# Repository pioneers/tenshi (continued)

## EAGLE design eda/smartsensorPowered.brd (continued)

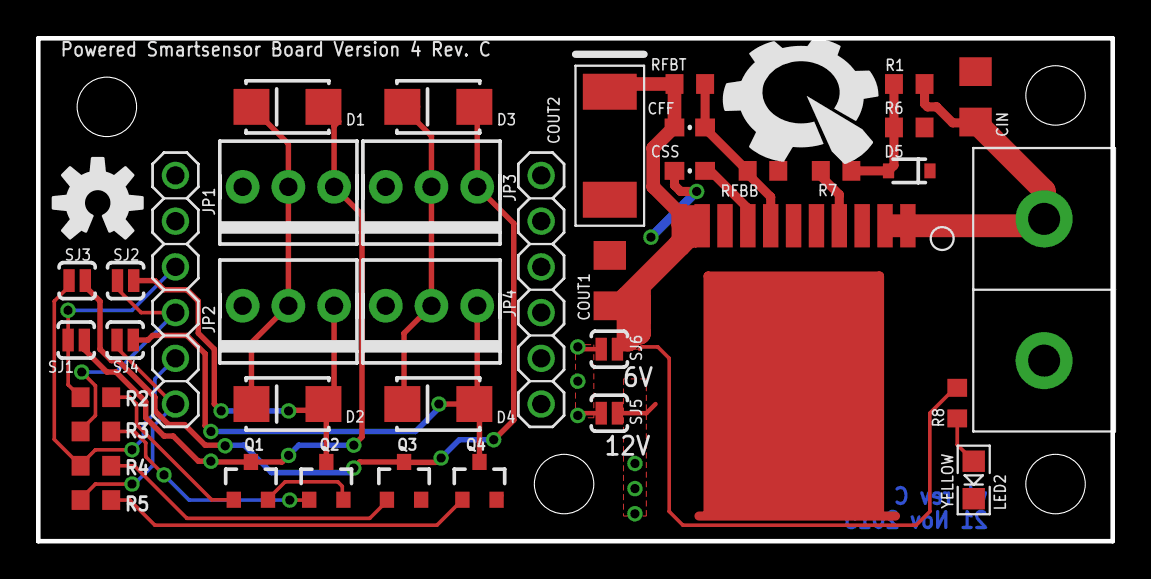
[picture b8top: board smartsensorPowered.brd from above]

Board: 2 copper layers, 59.7 x 27.9 mm, 45 parts (0 on the bottom side), 21 nets.

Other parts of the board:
U$2: PIE-LOGO-SMALL
U$4, U$5, U$6, U$7: STAND-OFF
U$10: OSHW-LOGO-M

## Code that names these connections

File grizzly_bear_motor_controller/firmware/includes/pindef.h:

#ifndef PINDEF_H
#define PINDEF_H

#define REV_A

#ifdef REV_A

// dip switch address select
#define PINDEF_DIP1             PF1
#define PINDEF_DIP2             PF4
#define PINDEF_DIP3             PF5
#define PINDEF_DIP4             PD3
#define PINDEF_DIP5             PF6
#define PINDEF_DIP6             PF7

// rotary encoder
#define PINDEF_ENCA             PB0
#define PINDEF_ENCB             PB4

// high side driver endable
#define PINDEF_HIGHSIDEENABLE   PE2

#endif

#endif

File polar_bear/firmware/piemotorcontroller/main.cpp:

/*
 * Berkeley Pioneers in Engineering
 * PiE Motor Controller Firmware
 * 
 */

#include <avr/io.h>
#include <avr/interrupt.h>
#define __DELAY_BACKWARD_COMPATIBLE__
#include <util/delay.h>
#include "Wire.h"

#define ENABLE_LEDS

//I2C bus address (hardcoded)
uint8_t I2C_ADDRESS = 0x0C;

/** Pin Definitions **/
//H-Bridge
const uint8_t IN1 =  PD4; //forward
const uint8_t IN2 =  PD5; //reverse (brakes if both IN1 and IN2 set)
const uint8_t D1  =  PD6; //disable (normally low)
const uint8_t D2  =  PD7; //disable (normally high)
const uint8_t FS  =  PB2; //fault status (currently not used)
const uint8_t FB  =  PC0; //feedback (also ADC0)
const uint8_t EN  =  PC1;
//Encoders
const uint8_t ENCA = PD2;
const uint8_t ENCB = PD3;
//LEDs
const uint8_t LED_RED   = PB0;
const uint8_t LED_GREEN = PB1;

//buffer size
const uint8_t BUFFER_SIZE = 255;
//Buffer
uint8_t reg[BUFFER_SIZE];
//current buffer address pointer
uint8_t addr = 0;

//////////// LED DEFINITIONS /////////////
void setupLEDs(){
	DDRB |= _BV(1) | _BV(0); //set pins as output for LEDs
}

/////////// Register Definitions ///////////
#define directionReg    (*((uint8_t *)(reg+0x01)))
#define pwmReg          (*((uint8_t *)(reg+0x02)))
#define feedbackReg     (*((uint16_t*)(reg+0x10)))
#define encoderCountReg (*((int32_t *)(reg+0x20)))
#define timeoutReg      (*((uint16_t*)(reg+0x80)))
#define stressReg       (*((uint8_t *)(reg+0xA0)))
#define nyanReg         (*((uint8_t *)(reg+0xA1)))

/////////// Motor Filter Registers ////////////

int16_t slewRateLimitedMotorV;
int16_t currentLimitedMotorV;
uint8_t finalMagnitude;
uint8_t finalDirection;

uint16_t timeSinceLastCommand = 0;  //Used for timeout in timer 2

///////////////////////////////////////////////

void setup();
void loop();
void receiveEvent(int count);
void requestEvent();
void setMotorDir(uint8_t dir);
void setMotorPWM(uint8_t value);
uint16_t readFeedback();

void motorSetup()
{
  // Set I/O Pins

  // Set IN1, IN2, D1, D2 as outputs
  DDRD |= (1 << IN1) | (1 << IN2) | (1 << D1) | (1 << D2);
  // Set EN as output
  DDRC |= (1 << EN);
  
  //Set EN
  PORTC |= (1 << EN);
  //Set D2
  PORTD |= (1 << D2);

  // Set FS pin as input, pull up enabled
  DDRB &= ~(1 << FS);
  PORTB |= (1 << FS);
  
  //Set Feedback pin as input
  DDRC &= ~(1 << FB);

  // Set up motor pwm (Timer 0)
  // Set Timer 0 to phase-correct PWM, output on OC0A
  TCCR0A |= (1 << WGM00) | (1 << COM0A1);
  // Set clock source to F_CPU/64
  TCCR0B |= (1 << CS01)|(1 << CS00);
  //~3922kHz
}

void setupEncoder(){
  EICRA = 0x05;
  EIMSK = 0x03;
  //DDRD &= ~( (1 << ENCA) & (1 << ENCB) );
  sei();
}

//utility functions
int16_t max(int16_t a,int16_t b){
    if(a > b){
        return a;
    }
    else{
        return b;
    }
}
int16_t min(int16_t a,int16_t b){
    if(a > b){
        return b;
    }
    else{
        return a;
    }
}
int16_t abs(int16_t a){
    if(a < 0){
        return -a;
    }
    else{
        return a;
    }
}

int main(void)
{
	encoderCountReg = 5;
	feedbackReg = 5;
	sei();
	setup();
	for(;;){
 		loop();
	}
}

//called on startup
void setup()
{
  //Setup I2C
  Wire.begin(I2C_ADDRESS);
  Wire.onReceive(receiveEvent);
  Wire.onRequest(requestEvent);
  
  //Setup Digital IO Pin directions
  motorSetup();
  
  setupLEDs();
  
  setupEncoder();
  
  //Setup timer 2
  // Set clock source to F_CPU/256
  TCCR2B |= (1<<CS22)|(1<<CS21)|(1<<CS20);
  //Enable Overflow interrupt
  TIMSK2 |= (1<<TOIE2);
  
  ///Default timeout is 100 iterations of timer2
  timeoutReg = 122;
}

//called continuously after startup
void loop(){
  //setMotorDir(directionReg);
  //setMotorPWM(pwmReg);
  setMotorDir(finalDirection);
  setMotorPWM(finalMagnitude);
  
  while(stressReg){
  	setMotorDir(1);
  	setMotorPWM(pwmReg);
  	_delay_ms(stressReg*10);
  	
  	setMotorDir(0);
  	setMotorPWM(pwmReg);
  	_delay_ms(stressReg*10);
  }
  
  
}

//called when I2C data is received
void receiveEvent(int count){
  timeSinceLastCommand = 0;
  //set address
  addr = Wire.receive();
  //read data
  while(Wire.available()){
    //write to register
    reg[addr++] = Wire.receive();
  }
}

//called when I2C data is reqested
void requestEvent()
{
  Wire.send(reg[addr++]);
}

//set motor direction
//Params:
//   byte dir:  1=fwd, 0=rev, 2=break
void setMotorDir(uint8_t dir){
  //set direction
  if (dir == 1){
    //set direction forward
    PORTD |=  (1<<IN1);
    PORTD &= ~(1<<IN2);
    
    //set LED Green
    #ifdef ENABLE_LEDS
    PORTB &= ~(1<<LED_RED);
    PORTB |=  (1<<LED_GREEN);
    #endif
  }
  else if (dir == 0){
    //set direction backward
    PORTD &= ~(1<<IN1);
    PORTD |=  (1<<IN2);
    
    //set LED RED
    #ifdef ENABLE_LEDS
    PORTB |=  (1<<LED_RED);
    PORTB &= ~(1<<LED_GREEN);
    #endif
  }
  else if (dir == 2){
    //set braking
    PORTD |=  (1<<IN1);
    PORTD |=  (1<<IN2);
    
    //set LEDs OFF
    #ifdef ENABLE_LEDS
    PORTB &= ~(1<<LED_RED);
    PORTB &= ~(1<<LED_GREEN);
    #endif
  }
}

//Set motor PWM value (between 0-255)
void setMotorPWM(uint8_t value){
  //set pwm
  OCR0A = 255-value;
}

//Encoder A Interrupt
ISR(INT0_vect)
{
  if( PIND & (1<<ENCA) ){
    if( PIND & (1<<ENCB) ){
      encoderCountReg--;
    }
    else{
      encoderCountReg++;
    }
  }
  else{
    if( PIND & (1<<ENCB) ){
      encoderCountReg++;
    }
    else{
      encoderCountReg--;
    }
  }
}

ISR(INT1_vect)
{
  if( PIND & (1<<ENCA) ){
    if( PIND & (1<<ENCB) )
      encoderCountReg++;
    else
      encoderCountReg--;
  }
  else{
    if( PIND & (1<<ENCB) )
      encoderCountReg--;
    else
      encoderCountReg++;
  }
}

uint16_t readFeedback(){
    uint8_t lowbyte, highbyte;
    
    PRR &= ~(1<<PRADC);    
    ADCSRA = (1<<ADPS2)|(1<<ADPS1)|(1<<ADPS0)|(1<<ADEN); //enable adc1(ADCEN)
    ADCSRB = 0x00;//free running mode
    ADMUX = 1<<REFS0;//select pin 0 and set reference to AVcc
    ADCSRA |= 1<<ADSC;//start conversion
    while( ADCSRA & (1<<ADSC) ){
        //wait for ADC Result
    }
    lowbyte = ADCL;
    highbyte = ADCH & 0x03;
    return lowbyte | ((uint16_t)highbyte)<<8;
}

//Timer 2 Interrupt
uint16_t overspikes = 0;
uint16_t max_overspikes = 50;
uint16_t period = 250;

uint16_t feedback_limit = 200;

uint16_t iterations_this_period = 0;

uint8_t rampingDown = 0;
uint8_t rampingUp = 0;

uint8_t rampupLimit = 0;
uint8_t rampDownLimit = 255;

ISR(TIMER2_OVF_vect)
{
  if( directionReg==2 ){
    finalMagnitude = pwmReg;
    finalDirection = 2;
    return;
  }
  
  iterations_this_period++;
  
  ////////// Timeout
  
  timeSinceLastCommand++;
  if(timeSinceLastCommand > timeoutReg && timeoutReg != 0){
    pwmReg = 0;
  }
  
  ////////// Slew rate limit
  
  if(directionReg == 0){
    slewRateLimitedMotorV = -pwmReg;
  }
  else{
    slewRateLimitedMotorV = pwmReg;
  }
  
  
  ////////// Current Limit 
  
  //check if period is over
  if(iterations_this_period > period){
    iterations_this_period = 0;
    if(rampingDown){
       rampingDown = 0;
       rampupLimit = 128;
       rampingUp = 1;
    }
    else if(rampingUp){
       rampingUp = 0;
    }
    overspikes = 0;
  }
  
  //Check if we have drawn too much current yet
  if(overspikes > max_overspikes){
    //start rampdown
    rampingDown = 1;
    rampDownLimit = abs(currentLimitedMotorV);
    rampingUp = 0;
    overspikes = 0;
    iterations_this_period = 0;
  }
  
  //read current feedback analog pin
  feedbackReg=readFeedback();
  //check if it exceeds our limit
  if(feedbackReg > feedback_limit){
    overspikes++;
  }
  
  
  if( rampingDown ){
    if( rampDownLimit > 128 ){
      rampDownLimit--;
    }
    int16_t directionalRampDownLimit;
    if( directionReg == 1 ){
        directionalRampDownLimit = rampDownLimit;
        currentLimitedMotorV = min(directionalRampDownLimit, slewRateLimitedMotorV);
    }
    else{
        directionalRampDownLimit = -rampDownLimit;
        currentLimitedMotorV = max(directionalRampDownLimit, slewRateLimitedMotorV);
    }
  }
  else if( rampingUp ){
    if( rampupLimit < 255 ){
        rampupLimit++;
    }
    int16_t directionalRampupLimit;
    if( directionReg == 1 ){
        directionalRampupLimit = rampupLimit;
        currentLimitedMotorV = min(directionalRampupLimit, slewRateLimitedMotorV);
    }
    else{
        directionalRampupLimit = -rampupLimit;
        currentLimitedMotorV = max(directionalRampupLimit, slewRateLimitedMotorV);
    }
  }
  else{
    currentLimitedMotorV = slewRateLimitedMotorV;
  }
  reg[0xA1] = rampingUp;
  reg[0xA2] = rampingDown;
  reg[0xA3] = iterations_this_period;
  reg[0xA4] = rampDownLimit;
  
  finalMagnitude = abs(currentLimitedMotorV);
  finalDirection = currentLimitedMotorV > 0;
}

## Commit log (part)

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2014-08-14 Initialize radio from main.c
2014-08-14 More informative hard fault handler for debugging
2014-08-14 Initialize tenshi runtime from main.c
2014-08-14 More garbage collect calls in runtime
2014-08-14 Example of how to hook up stdio to radio
2014-08-14 Replace runtime .lua files with compiled versions
2014-08-14 Controller radio throttling print statements
2014-08-14 More robust smart sensor recieving active packets
2014-08-14 Reduce stack size of uart driver
2014-08-28 Add dev.sh.
    Because we really don't need build.sh to develop angel-player.
2014-08-28 Add build-angel-player.sh.
    This script has the fewest dependencies to build and test angel player.
2014-08-28 Refactor dependencies for build-angel-player.sh.
    Now, you can build angel-player with only the essentials and emcc.
2014-08-28 Update README.md to emphasize OS independence.
2014-08-28 Add branding info.
    Among nice things this provides, viewSource.xul will actually work.
2014-08-28 New smart sensor type: Battery Buzzer (skeleton code)
2014-08-29 Smart sensor firmware: fix function prototype
2014-08-29 New smart sensor deploy script that takes the sensor type as an argument and inserts an appropriate ID and descriptor into the hex file before flashing
    Only digital-in sensors are supported so far
2014-08-29 Make COBS decode safer for malformed packets
2014-08-29 Change range of analog readings in student code to [0, 1] (assuming analog sensors send 10-bit values)
2014-08-29 Support for all four smart sensor busses on the controller
2014-08-29 Update to the smart sensor protocol doc. A new mode channel corresponding to the game mode.
2014-08-29 Cleanup digital smart sensor code
2014-08-29 Add game mode channel to descriptor for all sensors
2014-08-29 Add NDL3 and Lua objects to controller build script
2014-08-29 Send code strings in radio.js
2014-08-29 Added smartsensor variation checkboxes.
    On smartsensor.brd and smartsensorPowered.brd.
    Minor via shifting to accomodate text.
2014-08-29 Increase number of NDL3 ports to 5.
2014-08-29 Re-port xbee accumulator code.
2014-08-29 Smart sensor deploy script prints out the new ID
2014-08-29 Temporarily Reduce smart sensor protocol memory usage
2014-09-04 Add 5-pin smartsensor connector to lib
2014-09-06 Fix device pinout for 2x5 connectors
2014-09-08 Change smartsensor connector to 2x5 on grizzly bear
2014-09-08 Minor routing fixes on grizzly and controller.
2014-09-20 Bump version numbers
2014-09-25 Fix analog-in to read multiple inputs
2014-10-09 Added memory pool allocator implementation
    This memory pool allocator uses a bitfield to track allocations.
    It is restricted to 32 blocks total, but should be fairly efficient.
    Allocation and deallocation should be O(1).
2014-10-11 Add checkxip function for ARM uC
2014-10-11 Run code from ROM patch 1/5 -- ZIO "direct mode"
    This patch series is derived from some of the work done on eLua. Specifically,
    this set of patches is derived from
    https://github.com/elua/elua/commit/d54659b5723bcd2b1e3900362398c72c18a9aa0b.
    This commit changes lzio to handle a "direct mode" where it does not actually
    buffer and read data but instead directly exposes the backing pointer (which
    is most likely pointing into ROM). Note that this patch does not cover all
2014-10-11 Run code from ROM patch 4/5 -- Actual ROM chunk support
    This patch adds the actual changes in lundump to handle creating a function
    Proto that has code pointing to ROM.
2014-10-11 Implement eLua pseudo-RO strings
    These strings contain the actual string bytes in ROM. However, the TString
    object is still stored in RAM and contains a pointer to the ROM data where
    the string bytes would normally live. Note that if a pseudo-RO string gets
    GC'd and recreated, it most likely will no longer be a pseudo-RO string.
2014-10-11 Move even more items to CCM ram
2014-10-11 Force a bit more stuff into CCM ram
2014-10-11 Port uart_serial_driver to use packet pools
2014-10-11 Hack things until it does not instantly run out of RAM
2014-10-16 Style changes to mboxlib.c
2014-10-16 compiler error fix in mboxlib.c
2014-10-26 Update smartdevice.txt to use 2x5 header.
2014-10-26 Change smart sensor -> smart device in documentation.
2014-10-26 Change setGameMode to a public function
2014-10-26 Initial code for radio config thread and device enumeration
2014-11-01 Fix routing of smartsensor board after 2x5 change.
    The arrangement of the VCC/GND planes and overlapping pads of the
    sideways smartsensor conenctor interact in a strange way and
    cause EAGLE to not clearly indicate the presence of airwires.
    This commit repairs the airwires introduced in the 2x4 --> 2x5 change
    that were hidden by this idiosyncracy of EAGLE.
2014-11-06 Added a priority queue data structure for the runtime
    This is a priority queue implemented using a binary heap stored in
    an array. The priority queue will be used to implement wakeup events
    or other types of events in the runtime.
2014-11-08 Improve congested behavior of unreliable ports.
    Kick out the newest packet received so far, instead of dropping the
    incoming packet.
    Also, when a packet times out on an unreliable port, drop it.
2014-11-09 Add semi-colons
2014-11-09 Rewrote actor scheduler to not use Lua objects
    The actor scheduler now uses native C structs to manage the run
    queues rather than using "structs" that exist within Lua tables.
2014-11-09 Refactor a bunch of runtime lib loading to new file
2014-11-13 Start work on debugging value_update.
2014-11-13 Utkarsh: write ss_get_generic_val
2014-11-14 BUILD. Also modify protocol yaml to include 0x25
2014-11-14 Prelim linescan code
2014-11-14 Prelim linescan
2014-11-15 Rewrite timeouts to use a priority queue
2014-11-16 Implemented battery buzzer functionality
    The battery buzzer sends voltage measurements to the controller board
    as well as sounding an audible alarm if battery cell voltages are outside
    an acceptable range.
2014-11-16 Implemented smart device for line scan camera
    This is a linear camera with a clk and analog voltage output that
    will be used for Starwhal.
2014-11-23 Moved Vreg components. Moved passives near high side driver. Provided tkeepout range around the 5pin shrouded connector.
2014-11-23 Replaced connectors on controller with 2x5 shrouded. Also changed mounting hole spacing to 2.5 in.
2014-11-24 Receive PiEMOS data using new radio task.
2014-11-24 Add PiEMOS to runtime interface.
2014-11-25 changed rev number and pogo-pin positions on smartsensor_powered_jig
2014-11-25 battery buzzer and jig pogo pin changes/fixes
2014-12-04 i think this should result in my buzzer changes preserved, and still have the newest eda changes
2014-12-04 Minor typos... sorry.
2015-10-02 New EAGLE "package" for 1x6 pin header that adds wire strain relief holes.
2015-10-03 Add LT323 5V voltage regulator to the EAGLE library
2015-10-03 LED power light on Beaglebone Black cape
2015-10-04 Many fixes to PiE EAGLE library and Beaglebone top board
2015-10-04 New Arduino shield PCB that allows an Arduino to be a smart device
    This board allows the Hibike project to develop code for the different smart
    devices without requiring an unpowered smart device. It connects between
    the Arduino and either unpowered sensors, the powered smart device board,
    the battery buzzer, or the team flag through male/female header pins or pogo
    pins.
    This can also potentially be used as a test jig just by reprogramming the
2015-10-07 Version 4 smartsensor, still working on routing.
2015-10-08 Battery Buzzer Changes
2015-10-08 Got rid of unnecessary files
2015-10-09 finished changes after review 10-08-15
2015-10-09 Update layout of Arduino smart device shield to final smart device connector layout (rev A)
2015-10-09 New Arduino shield PCB that allows an Arduino to be a smart device
    This board allows the Hibike project to develop code for the different smart
    devices without requiring an unpowered smart device. It connects between
    the Arduino and either unpowered sensors, the powered smart device board,
    the battery buzzer, or the team flag through male/female header pins or pogo
    pins.
    This can also potentially be used as a test jig for programming the semart
2015-10-27 Update labels for Rev B. Add four extra status LEDs. Align board to origin. Move some silkscreen.
2015-10-29 Updated revision data on the cape board
2015-10-31 Fix silkscreen on Beaglebone top board #2
    - Put c1 and c2 in the same orientation
    - The 2x20 header pints are a single part. They mayt be selected at the
    bottom right cross on the .brd file
    - Tidied up component labels
2015-10-31 Fix for smartsensorPowered .brd .sch #2 - Changed the name of N$1 N$2 N$S N$4 to 6V_IF_SERVO1/2/3/4 - Ripped up redundant wire from cout1 - Casey explained that Vout connected by a polygon to a botto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
2015-11-05 Edited smartsensor, committing version B. Took out FTDI and similar parts, rerouted the whole thing, and changed the silkscreen.
2015-11-05 Fix for smartsensorPowered brd and sch #3 - aligned the JP connectors properly - Changed Rev from Rev. C to Rev. B
2015-11-05 Edited smartsensor, committing version B. Took out FTDI and similar parts, rerouted the whole thing, and changed the silkscreen.
    Updated 6-pin header for IO6-9 to 7-pin header for IO6-10.
2015-11-05 Update SMD header part, finish routing GND, update dates
2015-11-06 Team Flag: Update labels for Rev B. Add four extra status LEDs. Use SMD headers. Align board to origin. Move some silkscreen.
2015-11-06 Fix Beaglebone top board (Woodstock) for Rev B
    - Change name from "Top Board" to "Woodstock"
    - Switched the 12V and GND label to make it correct
    - Change size of drill hole for ethernet cutout from 1.25 to 0.75
    - Change 2.2uF capacitor to 2.2uF a polarised Tantalum Capacitor
    - Put c1 and c2 in the same orientation
    - Tidied up component labels
2015-11-06 Battery Buzzer Rev B fix ground pin, clean up labels
2015-11-07 fixed up metal detector board
2015-11-07 New metal detector smartsensor board (name not finalized)
2015-11-14 Add vertical variant to USB-OTG device
2015-11-21 Change ground indicator on silkscreen
2015-11-22 Add status LED to smartsensor
2015-11-27 Revision B of Arduino smart device shield
    - Add a connector for an external AVR programmer
2015-11-27 Move all traces to top layer
2015-11-28 pie.lbr: Add USB Micro-AB vertical package and add variant to USB-OTG device
2015-11-28 Rev C of Woodstock, minor changes
    - Update revision info
    - Make the power connector holes bigger to fit the actual wires
    - Change color or power LED to yellow to be more consistent with power LEDs on
    Grizzly and powered smartsensor
    - Change the board dimensions to go around the ethernet cutout. Hopefully Bay
    Area Circuits will cut the board to this shape. I left the perforation holes
2015-11-28 Woodstock fix vector font
2015-11-29 Use a plane to fix power plane connection
2015-11-29 Smartsensor move vias away from pads to reduce change of short while soldering
2015-12-03 Rename "Unpowered Smartsensor" to "Smartsensor" and move vias
    Move vias away from pads to reduce change of short while soldering
2016-06-18 Add links for mta and header pins
2016-07-02 Fix minutiae and add part info for circuit breaker and fuse holder
2016-07-02 Trial2
2016-07-07 Removed unnecessary temp files
2016-07-07 Eliminated Overlaps
2016-07-09 Renamed Board to PDB_SR
2016-07-09 Moved Holes toward outer edges
2016-07-16 Change names, broaden polygons, remove thermals, reformat sch
2016-08-01 Add datasheets for blutooth Andersons, 8 pin SOIC, 24 pin TSSOP, and TO-220 package
2016-08-13 Remove unnecessary files
2016-08-27 Add Buck_Connector package with correct dimensions and via sizes. Needs silkscreen notes.
2016-08-27 Created Buck_Converter Part
2016-08-28 Renamed Wires according to naming conventions
2016-08-28 Clean up circuit breaker symbol
2016-09-01 Add 5V rail to Board layout
2016-09-08 Add copyright and 5V rail polygons
2016-09-08 Correct add via layers to tValue
2016-09-15 Fix overlap and reroute schematic.
2016-09-20 Quick overhaul of DRU and LBR
    Add description and links for BBB and AMP
    Add a better description for the DRU and how it was adopted for PiE's
    use, modelled for Advanced Circuits
    Add wago screw terminals 2,3,4 pin
    TODO: Make sure the dimensions are correct, possibly even create new
    parts to fit the current screw terminals in stock
2016-09-22 VNH2SP30 device updated
2017-01-09 Changes to PDF Generation
    Stylistic changes & more pages to the board PDF
    also did several changes to the BOM generation, made it to work with run
    bom.ulp.
    The second change likely broken compatability with the tenshi specific
    bom scripts.
2017-01-09 Add vias to board PDFs in docu packets
    Add the vias to the board images that show traces.
